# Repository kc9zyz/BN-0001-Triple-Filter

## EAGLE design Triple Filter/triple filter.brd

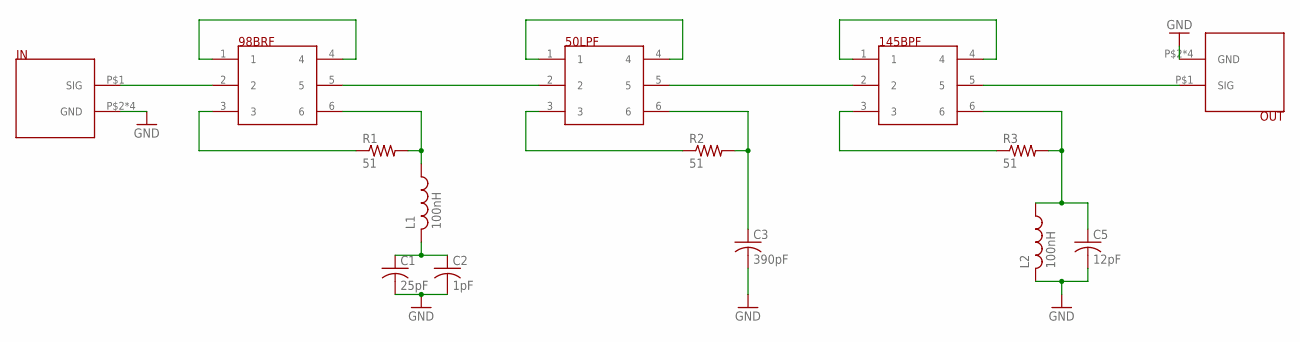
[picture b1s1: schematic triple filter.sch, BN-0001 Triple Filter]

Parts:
50LPF, 98BRF, 145BPF: JS202011SCQN
C1: 25pF; C0805
C2: 1pF; C0805
C3: 390pF; C0805
C5: 12pF; C0805
IN: SMA-CONN
L1, L2: 100nH; L2012C
OUT: SMA-CONN
R1, R2, R3: 51; R0805

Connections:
GND: C1.2, C2.2, C3.2, C5.2, IN.P$2 (GND), IN.P$3 (GND), IN.P$4 (GND), IN.P$5 (GND), L2.2, OUT.P$2 (GND), OUT.P$3 (GND), OUT.P$4 (GND), OUT.P$5 (GND)
unnamed: 98BRF.1, 98BRF.4
unnamed: C1.1, C2.1, L1.2
unnamed: 98BRF.2, IN.P$1 (SIG)
unnamed: 145BPF.5, OUT.P$1 (SIG)
unnamed: 98BRF.3, R1.1
unnamed: 50LPF.1, 50LPF.4
unnamed: 50LPF.2, 98BRF.5
unnamed: 50LPF.3, R2.1
unnamed: 50LPF.5, 145BPF.2
unnamed: 145BPF.1, 145BPF.4
unnamed: 145BPF.3, R3.1
OUT1: 98BRF.6, L1.1, R1.2
OUT2: 50LPF.6, C3.1, R2.2
OUT3: 145BPF.6, C5.1, L2.1, R3.2

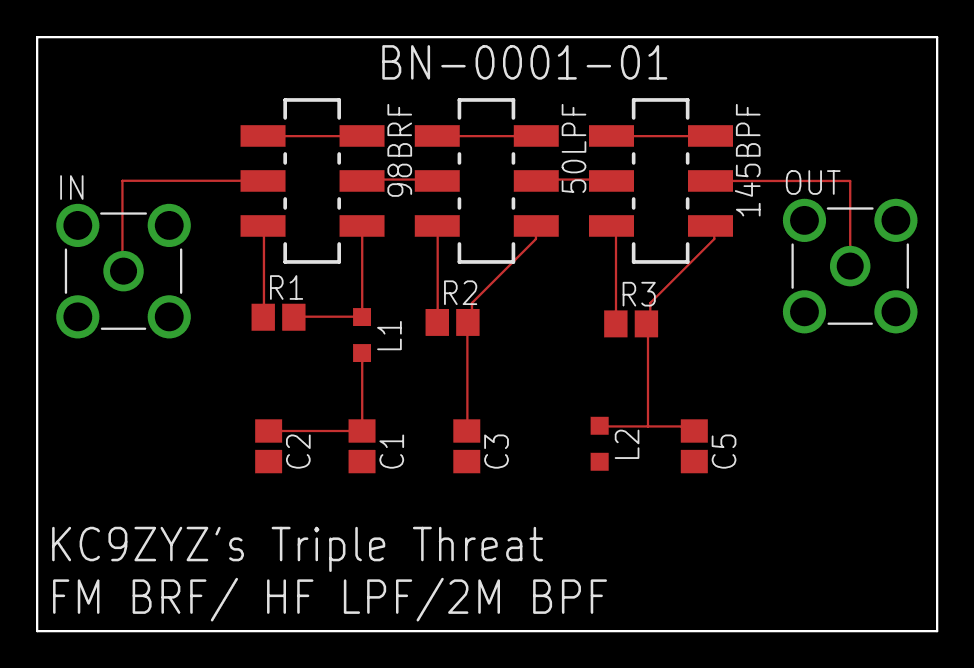
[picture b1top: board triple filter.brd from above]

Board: 2 copper layers, 50.0 x 33.0 mm, 14 parts (0 on the bottom side), 15 nets.

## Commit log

2015-04-22 Initial Commit with board revision 01
2015-04-22 Added Gerber files and brd/sch images
2015-04-22 Added gerber composite simulation
